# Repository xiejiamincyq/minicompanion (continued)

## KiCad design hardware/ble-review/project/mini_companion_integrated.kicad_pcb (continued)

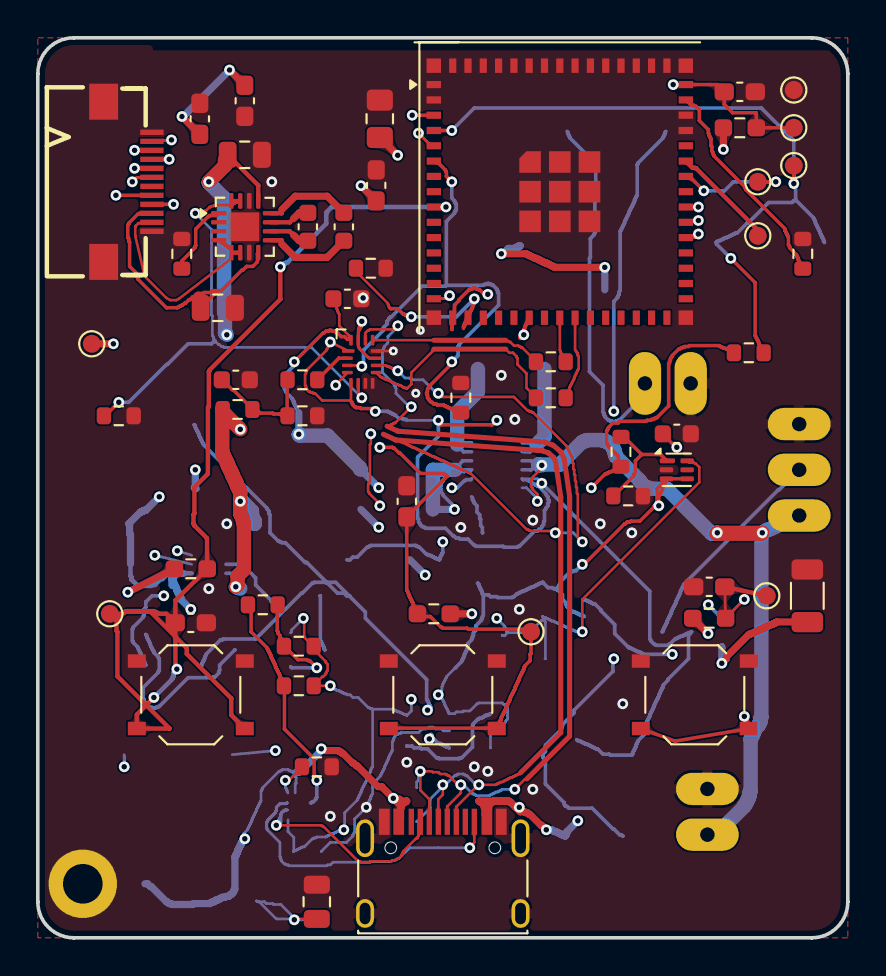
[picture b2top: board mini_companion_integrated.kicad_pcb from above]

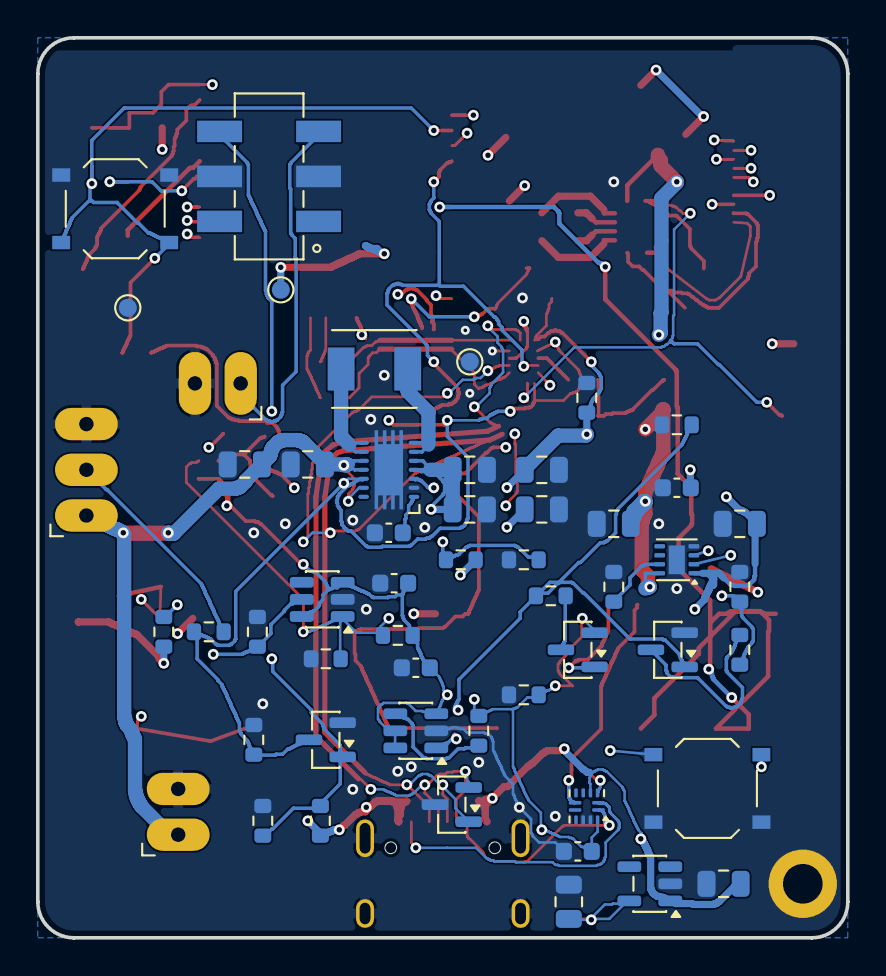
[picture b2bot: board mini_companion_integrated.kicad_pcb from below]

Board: 4 copper layers, 45.0 x 50.0 mm, 110 parts (53 on the bottom side), 58 nets.

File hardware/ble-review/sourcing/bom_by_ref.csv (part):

ref,category,assembly_domain,value,mpn,manufacturer,lcsc,footprint,qty_per_device,quantity_two,unit,source,stock_status,smt_catalog_status,source_url,note
C101,electronics,main,22µ,CL21A226MAQNNNE,Samsung,C45783,Capacitor_SMD:C_0805_2012Metric_Pad1.18x1.45mm_HandSolder,1,2,piece,saved_netlist,未取得本轮国内库存/采购报价,待嘉立创按精确型号匹配,,
C102,electronics,main,100n,CC0603KRX7R9BB104,YAGEO,C14663,Capacitor_SMD:C_0603_1608Metric_Pad1.08x0.95mm_HandSolder,1,2,piece,saved_netlist,未取得本轮国内库存/采购报价,待嘉立创按精确型号匹配,,
C103,electronics,main,1µ,CL10A105KB8NNNC,Samsung,C15849,Capacitor_SMD:C_0603_1608Metric_Pad1.08x0.95mm_HandSolder,1,2,piece,saved_netlist,未取得本轮国内库存/采购报价,待嘉立创按精确型号匹配,,
C301,electronics,main,1µ,CL10A105KB8NNNC,Samsung,C15849,Capacitor_SMD:C_0603_1608Metric_Pad1.08x0.95mm_HandSolder,1,2,piece,saved_netlist,未取得本轮国内库存/采购报价,待嘉立创按精确型号匹配,,
C302,electronics,main,1µ,CL10A105KB8NNNC,Samsung,C15849,Capacitor_SMD:C_0603_1608Metric_Pad1.08x0.95mm_HandSolder,1,2,piece,saved_netlist,未取得本轮国内库存/采购报价,待嘉立创按精确型号匹配,,
C501,electronics,main,100n,CC0603KRX7R9BB104,YAGEO,C14663,Capacitor_SMD:C_0603_1608Metric_Pad1.08x0.95mm_HandSolder,1,2,piece,saved_netlist,未取得本轮国内库存/采购报价,待嘉立创按精确型号匹配,,
C502,electronics,main,100n,CC0603KRX7R9BB104,YAGEO,C14663,Capacitor_SMD:C_0603_1608Metric_Pad1.08x0.95mm_HandSolder,1,2,piece,saved_netlist,未取得本轮国内库存/采购报价,待嘉立创按精确型号匹配,,
C504,electronics,main,100n,CC0603KRX7R9BB104,YAGEO,C14663,Capacitor_SMD:C_0603_1608Metric_Pad1.08x0.95mm_HandSolder,1,2,piece,saved_netlist,未取得本轮国内库存/采购报价,待嘉立创按精确型号匹配,,
C604,electronics,main,22uF 25V X5R 20%,CL21A226MAQNNNE,Samsung,C45783,Capacitor_SMD:C_0805_2012Metric,1,2,piece,saved_netlist,未取得本轮国内库存/采购报价,待嘉立创按精确型号匹配,,Candidate; see source contract
C606,electronics,main,22uF 25V X5R 20%,CL21A226MAQNNNE,Samsung,C45783,Capacitor_SMD:C_0805_2012Metric,1,2,piece,saved_netlist,未取得本轮国内库存/采购报价,待嘉立创按精确型号匹配,,Candidate; see source contract
C607,electronics,main,22uF 25V X5R 20%,CL21A226MAQNNNE,Samsung,C45783,Capacitor_SMD:C_0805_2012Metric,1,2,piece,saved_netlist,未取得本轮国内库存/采购报价,待嘉立创按精确型号匹配,,Candidate; see source contract
C617,electronics,main,2.2uF 10V X7R 10%,CL21B225KPFNNNE,Samsung,C107366,Capacitor_SMD:C_0805_2012Metric,1,2,piece,saved_netlist,未取得本轮国内库存/采购报价,待嘉立创按精确型号匹配,,Candidate; see source contract
C618,electronics,main,470nF 25V X7R 10%,CL10B474KA8NNNC,Samsung,C1623,Capacitor_SMD:C_0603_1608Metric,1,2,piece,saved_netlist,未取得本轮国内库存/采购报价,待嘉立创按精确型号匹配,,Candidate; see source contract
C619,electronics,main,470nF 25V X7R 10%,CL10B474KA8NNNC,Samsung,C1623,Capacitor_SMD:C_0603_1608Metric,1,2,piece,saved_netlist,未取得本轮国内库存/采购报价,待嘉立创按精确型号匹配,,Candidate; see source contract
C620,electronics,main,2.2uF 10V X7R 10%,CL21B225KPFNNNE,Samsung,C107366,Capacitor_SMD:C_0805_2012Metric,1,2,piece,saved_netlist,未取得本轮国内库存/采购报价,待嘉立创按精确型号匹配,,Candidate; see source contract
C637,electronics,main,22uF 25V X5R 20%,CL21A226MAQNNNE,Samsung,C45783,Capacitor_SMD:C_0805_2012Metric,1,2,piece,saved_netlist,未取得本轮国内库存/采购报价,待嘉立创按精确型号匹配,,Candidate; see source contract
C638,electronics,main,22uF 25V X5R 20%,CL21A226MAQNNNE,Samsung,C45783,Capacitor_SMD:C_0805_2012Metric,1,2,piece,saved_netlist,未取得本轮国内库存/采购报价,待嘉立创按精确型号匹配,,Candidate; see source contract
C639,electronics,main,100nF 50V X7R 10%,CC0603KRX7R9BB104,YAGEO,C14663,Capacitor_SMD:C_0603_1608Metric,1,2,piece,saved_netlist,未取得本轮国内库存/采购报价,待嘉立创按精确型号匹配,,Candidate; see source contract
C640,electronics,main,22uF 25V X5R 20%,CL21A226MAQNNNE,Samsung,C45783,Capacitor_SMD:C_0805_2012Metric,1,2,piece,saved_netlist,未取得本轮国内库存/采购报价,待嘉立创按精确型号匹配,,Candidate; see source contract
C1101,electronics,main,100nF 50V X7R,CC0603KRX7R9BB104,YAGEO,C14663,Capacitor_SMD:C_0603_1608Metric,1,2,piece,saved_netlist,未取得本轮国内库存/采购报价,待嘉立创按精确型号匹配,,
C1102,electronics,main,100nF 50V X7R,CC0603KRX7R9BB104,YAGEO,C14663,Capacitor_SMD:C_0603_1608Metric,1,2,piece,saved_netlist,未取得本轮国内库存/采购报价,待嘉立创按精确型号匹配,,
C7101,electronics,main,2.2uF 50V X7R 10%,CL21B225KBYNNNE,Samsung,C2762602,Capacitor_SMD:C_0805_2012Metric,1,2,piece,saved_netlist,未取得本轮国内库存/采购报价,待嘉立创按精确型号匹配,,Candidate; see source contract
C7102,electronics,main,1uF 50V X7R 10%,CL21B105KBFNNNE,Samsung,C28323,Capacitor_SMD:C_0805_2012Metric,1,2,piece,saved_netlist,未取得本轮国内库存/采购报价,待嘉立创按精确型号匹配,,Candidate; see source contract
C7103,electronics,main,2.2uF 10V X7R 10%,CL21B225KPFNNNE,Samsung,C107366,Capacitor_SMD:C_0805_2012Metric,1,2,piece,saved_netlist,未取得本轮国内库存/采购报价,待嘉立创按精确型号匹配,,Candidate; see source contract
C7104,electronics,main,2.2uF 10V X7R 10%,CL21B225KPFNNNE,Samsung,C107366,Capacitor_SMD:C_0805_2012Metric,1,2,piece,saved_netlist,未取得本轮国内库存/采购报价,待嘉立创按精确型号匹配,,Candidate; see source contract
C7105,electronics,main,100nF 50V X7R 10%,CC0603KRX7R9BB104,YAGEO,C14663,Capacitor_SMD:C_0603_1608Metric,1,2,piece,saved_netlist,未取得本轮国内库存/采购报价,待嘉立创按精确型号匹配,,Candidate; see source contract
C7106,electronics,main,100nF 50V X7R 10%,CC0603KRX7R9BB104,YAGEO,C14663,Capacitor_SMD:C_0603_1608Metric,1,2,piece,saved_netlist,未取得本轮国内库存/采购报价,待嘉立创按精确型号匹配,,Candidate; see source contract
C7107,electronics,main,100nF 50V X7R 10%,CC0603KRX7R9BB104,YAGEO,C14663,Capacitor_SMD:C_0603_1608Metric,1,2,piece,saved_netlist,未取得本轮国内库存/采购报价,待嘉立创按精确型号匹配,,Candidate; see source contract
C7108,electronics,main,2.2uF 10V X7R 10%,CL21B225KPFNNNE,Samsung,C107366,Capacitor_SMD:C_0805_2012Metric,1,2,piece,saved_netlist,未取得本轮国内库存/采购报价,待嘉立创按精确型号匹配,,Candidate; see source contract
C7301,electronics,main,100nF 50V,CC0603KRX7R9BB104,YAGEO,C14663,Capacitor_SMD:C_0603_1608Metric,1,2,piece,saved_netlist,未取得本轮国内库存/采购报价,待嘉立创按精确型号匹配,,
C7302,electronics,main,100nF 50V,CC0603KRX7R9BB104,YAGEO,C14663,Capacitor_SMD:C_0603_1608Metric,1,2,piece,saved_netlist,未取得本轮国内库存/采购报价,待嘉立创按精确型号匹配,,
D7301,electronics,main,"PESD5V0U2BT,215","PESD5V0U2BT,215",Nexperia,C85399,Package_TO_SOT_SMD:SOT-23,1,2,piece,saved_netlist,国内实时库存和人民币数量价未知,JLCPCB国际目录标Extended及SMT；国内型号匹配待询,https://jlcpcb.com/partdetail/Nexperia-PESD5V0U2BT215/C85399,
EXT_CASE_SCREWS,hardware,external,M2x6 90deg countersunk case closure screw,TBD_M2X6_90DEG_COUNTERSUNK,,,,4,8,piece,baseline_external_scope_pending_final_mechanical_review,待完整报价,板外采购或装配工序,,"Exact supplier SKU, tolerance and torque unverified; different head from switch mounting screws."
EXT_CONSUMABLES,consumables,external,Solder/flux/cleaning and general assembly consumables,TBD_ASSEMBLY_CONSUMABLE_PURCHASE,,,,0.5,1,two-device purchase batch,baseline_external_scope_pending_final_mechanical_review,待完整报价,板外采购或装配工序,,代工商提供焊料/助焊剂/清洁剂并计入加工费；此行用于确认范围，不重复采购用户零售整包耗材
EXT_DELIVERY,delivery,external,All electronics/material/PCB/printing shipment charges,TBD_ALL_REQUIRED_SHIPMENTS,,,,0.5,1,all orders,baseline_external_scope_pending_final_mechanical_review,待完整报价,板外采购或装配工序,,"One ledger placeholder covers all shipments, not a claim of one parcel. No assumed free shipping, coupons or membership discount."
EXT_H101_SCREW,hardware,external,M2x5 board fixing screw,TBD_M2X5_H101_HEAD_UNFROZEN,,,,1,2,piece,baseline_external_scope_pending_final_mechanical_review,待完整报价,板外采购或装配工序,,H101 mounting hole is already in PCB; screw head style remains unresolved. No standoffs/tray screws/independent LCD or PCB clamp screws in current assembly.
EXT_LCD,external_electronics,external,Original 2-inch display,HS20HS072RX,HS,C5329582,,1,2,piece,baseline_external_scope_pending_final_mechanical_review,本轮公开文本未返回国内数量价/可用库存,国内页面有SMT扩展库标签，但本设计为板外插屏，不可混入主板贴装坐标,https://item.szlcsc.com/6087843.html,"Retain original display; its FPC receptacle is FPC301, not duplicated here."
EXT_LCD_TAPE,insulation_fixing,external,Soft double-sided LCD mounting tape,TBD_LCD_FLEXIBLE_TAPE_0.30MM,,,,4,8,small patch,baseline_external_scope_pending_final_mechanical_review,待完整报价,板外采购或装配工序,,Nominal0.30mm thickness. Buy quantity must follow actual roll/sheet MOQ; eight patches are consumption only.
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
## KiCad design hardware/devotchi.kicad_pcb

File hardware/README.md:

> 2026-11-19 · 此页保留早期设计背景。两台 BLE 样机从 [当前硬件入口](../hardware/ble-review/README.md) 进入。

# Hardware Design

## PCB

## Device Variants

### Portable WiFi+BLE (current)
- ESP32-S3-MINI-1 with integrated PCB antenna
- HS20HS072RX 2.0" color TFT LCD (ST7789, 320x240, IPS)
- LiPo battery, USB-C charging
- 3 buttons (approve, reject, action)
- Status LED, vibration motor
- Connects to server via WiFi, or to phone via BLE

### Portable Cellular (planned)
- Same form factor as WiFi+BLE version
- Additional cellular modem (MCU TBD — may use same ESP32-S3 + SIM module, or different MCU)
- SIM/eSIM support (provider TBD)
- Works standalone anywhere with cell coverage

### Desktop (planned)
- USB-powered (no battery needed)
- Potentially larger display
- Same ESP32-S3-MINI-1, connects via USB serial or WiFi

---

## Parts

See [purchase-list.md](purchase-list.md) for the complete BOM with LCSC part numbers and sourcing info.

### MCU: ESP32-S3-MINI-1-N4R2

| Spec | Value |
|---|---|
| Part number | ESP32-S3-MINI-1-N4R2 (4MB flash, 2MB PSRAM) |
| CPU | Dual-core Xtensa LX7 @ 240 MHz |
| SRAM | 512 KB + 2MB PSRAM |
| WiFi | 802.11 b/g/n, 2.4 GHz |
| Bluetooth | BLE 5.0 |
| Antenna | Integrated PCB antenna |
| Module dimensions | 15.4 x 20.5 x 2.4 mm |
| Operating voltage | 3.0 - 3.6V |

**Datasheets:** [Module](../docs/mcu/ESP32-S3-MINI-1_datasheet.pdf) | [SoC](../docs/mcu/ESP32-S3_SoC_datasheet.pdf)

**Why N4R2:** PSRAM needed for display framebuffers — 320x240 RGB565 = 150KB per frame, double buffering needs 300KB. Without PSRAM, internal 512KB SRAM can't fit framebuffers + WiFi stack + application.

### Display: HS20HS072RX 2.0" Color TFT LCD

| Spec | Value |
|---|---|
| Manufacturer | HS (Shenzhen Hansheng) |
| Part number | HS20HS072RX |
| LCSC | C5329582 |
| Driver IC | ST7789T3 |
| Size | 2.0 inches diagonal |
| Resolution | 320 x 240 pixels (QVGA) |
| Colors | 262K (RGB666) |
| Pixel pitch | 0.151 x 0.153 mm |
| Active area | 40.80 x 30.60 mm |
| Module size | 51.80 x 36.20 mm |
| Interface | SPI (4-wire) |
| Operating voltage | IOVCC 1.65-3.3V, VCI 2.4-3.3V |
| Backlight | 4 white LEDs in parallel, 80mA max |
| Backlight forward voltage | 3.0V typical (2.8-3.2V) |
| Sleep current | ~30 uA (SLPIN command) |
| Viewing angle | ALL directions (IPS) |
| Contrast ratio | 300:1 typical |
| Connector | 12-pin FPC, 0.5mm pitch |
| Connection type | COG + FPC |

**Datasheet:** [HS20HS072RX datasheet](../docs/display/HS20HS072RX_datasheet.pdf)

**Source:** [LCSC/JLCPCB C5329582](https://www.lcsc.com/product-detail/lcd-screen_hs-hs20hs072rx_C5329582.html) — $3.70 (1+), $2.49 (100+), 1687 in stock.

**Why this part:**
- Full RGB color — expressive Tamagotchi character (red angry, green happy, etc.)
- 320x240 resolution — excellent detail for pixel art and text
- IPS viewing angle — looks good from any direction (critical for handheld)
- Runs entirely on 3.3V — no boost converter needed (unlike OLED panels needing 12V VCC)
- ST7789 has first-class ESP-IDF support via built-in `esp_lcd` driver
- $2.49 at volume with 1600+ stock — cheap and available
- 12-pin FPC is simple to wire (vs 30-pin for OLED panels)
- Backlight can be PWM-dimmed via MOSFET for power saving

**FPC pinout:**

| Pin | Symbol | Description |
|---|---|---|
| 1 | GND | Power ground |
| 2 | CS | Chip select (active low) |
| 3 | RS (DC) | Data/command select |
| 4 | SCL | SPI clock |
| 5 | SDA | SPI data (MOSI) |
| 6 | RST | Reset (active low) |
| 7 | NC | No connect |
| 8 | IOVCC | I/O logic supply (3.3V) |
| 9 | VCC | Panel power supply (3.3V) |
| 10 | A | Backlight LED anode |
| 11 | K | Backlight LED cathode |
| 12 | GND | Power ground |

### Backlight Dimming Circuit

Backlight driven from +BATT (3.7-4.2V) through 22Ω resistor + AO3400A N-ch MOSFET, PWM-controlled by ESP32.

**Why +BATT instead of 3.3V:** LEDs have Vf = 3.0V. Only 0.3V headroom from 3.3V — poor regulation. +BATT gives 0.7-1.2V headroom.

**Circuit:** `+BATT → R (22Ω) → LED anode → LED cathode → MOSFET drain → GND`, gate driven by DISP_BL GPIO.

**Current at different battery voltages:**
- 4.2V (full): ~55mA | 3.7V (nominal): ~32mA | 3.4V (low): ~18mA

**Firmware:** PWM at 1kHz+. Sleep: SLPIN (0x10) + duty=0. Wake: duty>0 + SLPOUT (0x11), wait 120ms.

### Firmware Graphics Library

**Recommended: ESP-IDF native `esp_lcd` + LovyanGFX**

- `esp_lcd` provides the built-in ST7789 panel driver for SPI initialization
- LovyanGFX provides sprite-based graphics, text rendering, and animations
- LovyanGFX supports ESP-IDF natively (not Arduino-only)
- Supports DMA transfers for background rendering
- ST7789 sleep commands (SLPIN/SLPOUT) supported for power management
- Alternative: LVGL if more complex UI widgets are needed later

### Power Chain

USB-C → TP4056 (charger) → DW01A+FS8205A (protection) → ME6211 (3.3V LDO) → ESP32-S3 + display

**Datasheets:** [TP4056](../docs/power/TP4056_datasheet.pdf) | [DW01A](../docs/power/DW01A_datasheet.pdf) | [FS8205A](../docs/power/FS8205A_datasheet.pdf) | [ME6211](../docs/power/ME6211_datasheet.pdf)

**Key design notes:**
- TP4056 charge current set by R205 (3kΩ → ~330mA charge rate)
- DW01A+FS8205A: standard LiPo protection pair, back-to-back MOSFETs in battery ground path
- ME6211 LDO: 100mV dropout — at low battery (<3.4V) output sags below 3.3V, acceptable for MVP
- USB-C CC1/CC2 pull-downs: 5.1kΩ each for proper USB-C detection

### Buttons

3 tactile switches with hardware debounce (10kΩ pull-up + 100nF cap per button). Active low, pressed = GND. Any button press wakes from deep sleep.

| Button | Function |
|---|---|
| Approve | Accept approval/permission requests |
| Reject | Reject approval/permission requests |
| Action | Context-dependent: scroll, open menu, poke pet |

### Feedback

- **Debug LED** (green 0603) — GPIO direct drive through 150Ω resistor. Dev/debug only.
- **Vibration motor** (6mm coin, 3V) — AO3400A MOSFET driver + 1N5819W flyback diode. PWM-capable. Connected via solder pads.

---

## Pin Assignment

**Strapping pins to avoid:** GPIO0 (boot mode), GPIO3 (JTAG source, floating), GPIO45 (VDD_SPI), GPIO46 (boot mode). These are sampled at reset and should not have external loads that could affect their default state during boot.

| Function | ESP32-S3 GPIO | Notes |
|---|---|---|
| **SPI Display** | | |
| DISP_SCLK | GPIO 12 | SPI clock |
| DISP_MOSI | GPIO 11 | SPI data |
| DISP_CS | GPIO 10 | Chip select |
| DISP_DC | GPIO 9 | Data/command select |
| DISP_RST | GPIO 8 | Reset |
| DISP_BL | GPIO 13 | PWM via MOSFET to backlight cathode |
| **Buttons** | | |
| BTN_APPROVE | GPIO 4 | Pull-up, active low |
| BTN_REJECT | GPIO 5 | Pull-up, active low |
| BTN_ACTION | GPIO 6 | Pull-up, active low |
| **Feedback** | | |
| LED_PWM | GPIO 38 | PWM for brightness control |
| MOTOR_EN | GPIO 37 | Via N-channel MOSFET |
| **Power status** | | |
| PWR_CHRG | GPIO 18 | Low = charging |
| PWR_STDBY | GPIO 17 | Low = charge complete |
| BAT_ADC | GPIO 1 | Via voltage divider for battery level |
| **Future (unused, reserved)** | | |
| I2S BCLK | GPIO 15 | For microphone (voice commands) |
| I2S WS | GPIO 16 | For microphone |
| I2S DIN | GPIO 2 | For microphone (GPIO 17 used by PWR_STDBY) |

---

## Power Budget (estimated)

| State | ESP32-S3 | Display | Total | Battery life (500mAh) |
|---|---|---|---|---|
| **Active** (WiFi on, display on, backlight 100%) | ~80 mA | ~60 mA | ~140 mA | ~3.6 hours |
| **Idle** (WiFi connected, backlight 25%) | ~20 mA | ~15 mA | ~35 mA | ~14 hours |
| **Light sleep** (WiFi off, backlight off, LCD sleep) | ~2 mA | ~0.03 mA | ~2 mA | ~250 hours |
| **Deep sleep** (everything off) | ~8 uA | ~30 uA | ~38 uA | ~1.5 years |

Real-world usage will be a mix — display on for a few seconds when events arrive, then back to sleep. Expected practical battery life: **2-5 days** with typical AI coding session activity.

---

## Power Management Strategy

1. **Normal operation**: WiFi connected, display off. ESP32 in light sleep between events.
2. **Event arrives** (via WiFi): Wake up, turn on display, show status/approval, vibrate if needed.
3. **Approval request**: Display stays on with countdown timer until user responds or timeout.
4. **No activity for N minutes**: Enter deep sleep. Wake on any button press.
5. **Deep sleep**: Everything off. Battery lasts weeks/months.
6. **Display auto-off**: Display turns off after 30 seconds of no new events (configurable).

---

## PCB Design Notes

- **Single PCB** — power management and logic on one board
- Power section (TP4056, ME6211, USB-C, battery connector) on one side, logic section (ESP32, display connector, buttons) on the other
- Ground plane between sections
- ESP32-S3-MINI-1 antenna keepout zone respected (no copper/ground under antenna area)
- Display connects via 12-pin 0.5mm FPC cable (AFC01-S12FCA-00 connector)
- USB-C connector: 16-pin mid-mount type with D+/D- connected to ESP32-S3 USB OTG pins for firmware updates and serial communication
- Battery connector: JST-PH 2-pin SMD (standard for small LiPo, LCSC C7433648)
- Test points: 3.3V, +BATT, GND, UART TX/RX

---

## Enclosure

- 3D printed (material TBD: PLA, ABS, or PETG)
- Size determined after PCB layout and LiPo selection
- Rough estimate: ~50 x 40 x 20mm (similar to original Tamagotchi)
- Cutouts for: display window, 4 buttons, USB-C port, LED light pipe
- Optional clip or lanyard hole for portability

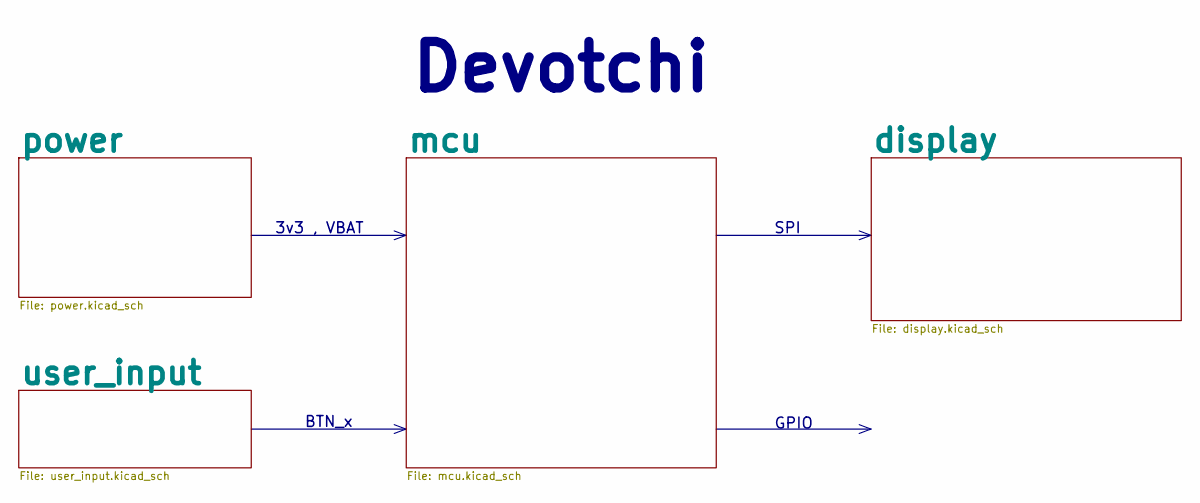
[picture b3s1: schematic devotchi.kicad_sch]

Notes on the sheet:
Devotchi
3v3 , VBAT
GPIO
SPI
BTN_x

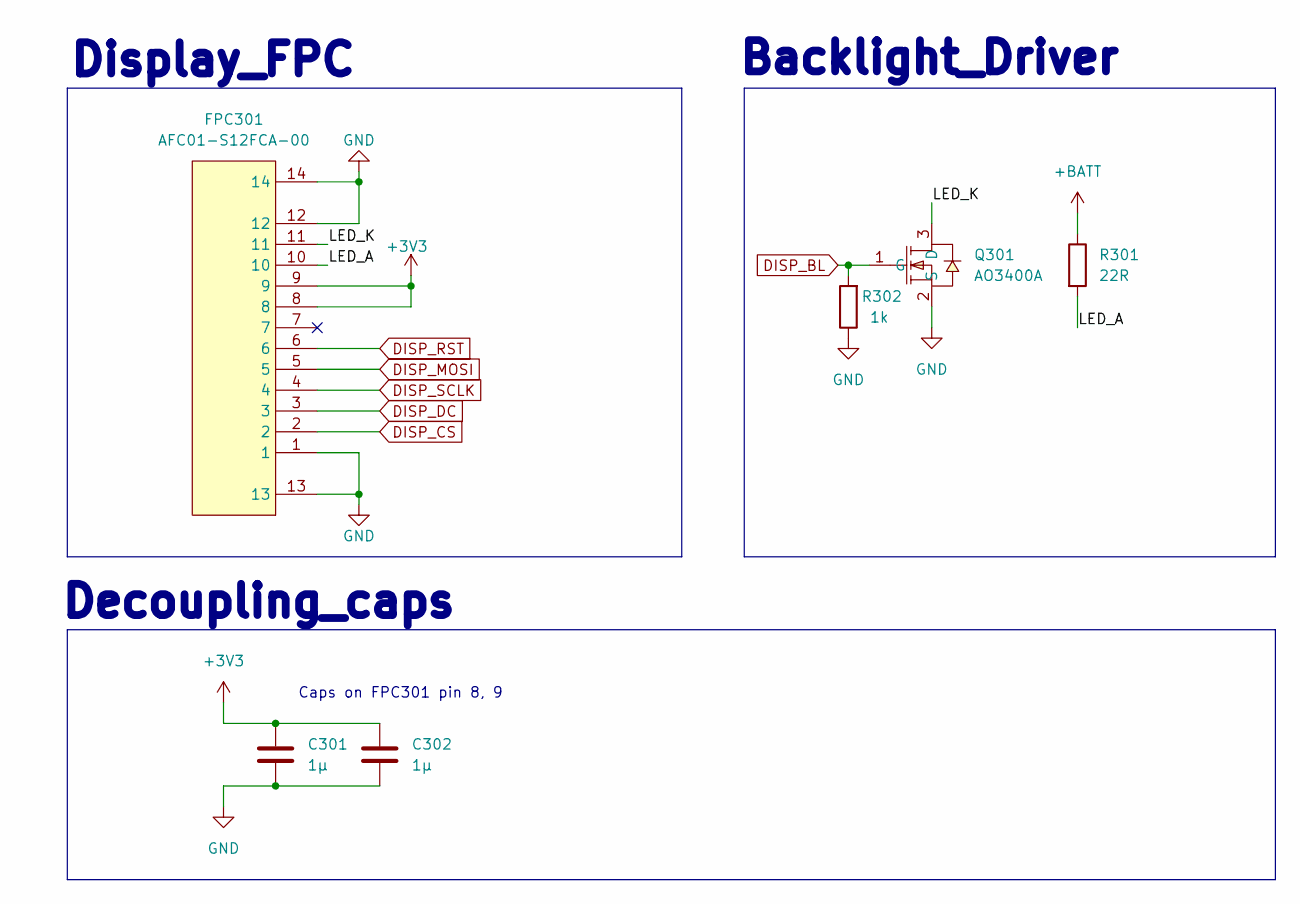
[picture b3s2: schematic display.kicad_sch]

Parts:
C301, C302: 1µ; C_0603_1608Metric_Pad1.08x0.95mm_HandSolder; LCSC Part C15849
FPC301: AFC01-S12FCA-00; FPC-SMD_AFC01-S12FCA-00; LCSC Part C262661
Q301: AO3400A; SOT-23-3_L2.9-W1.3-P1.90-LS2.4-BR; LCSC Part C20917
R301: 22R; R_0603_1608Metric_Pad0.98x0.95mm_HandSolder; LCSC Part C23345
R302: 1k; R_0603_1608Metric_Pad0.98x0.95mm_HandSolder; LCSC Part C21190

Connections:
+3V3: C301.1, C302.1, FPC301.8, FPC301.9; also elsewhere on the board
+BATT: R301.1; also elsewhere on the board
/display/LED_A: FPC301.10, R301.2
/display/LED_K: FPC301.11, Q301.3 (D)
DISP_BL: Q301.1 (G), R302.2; also elsewhere on the board
DISP_CS: FPC301.2; also elsewhere on the board
DISP_DC: FPC301.3; also elsewhere on the board
DISP_MOSI: FPC301.5; also elsewhere on the board
DISP_RST: FPC301.6; also elsewhere on the board
DISP_SCLK: FPC301.4; also elsewhere on the board
GND: C301.2, C302.2, FPC301.1, FPC301.12, FPC301.13, FPC301.14, Q301.2 (S), R302.1; also elsewhere on the board

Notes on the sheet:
Decoupling_caps
Caps on FPC301 pin 8, 9
Display_FPC
Backlight_Driver

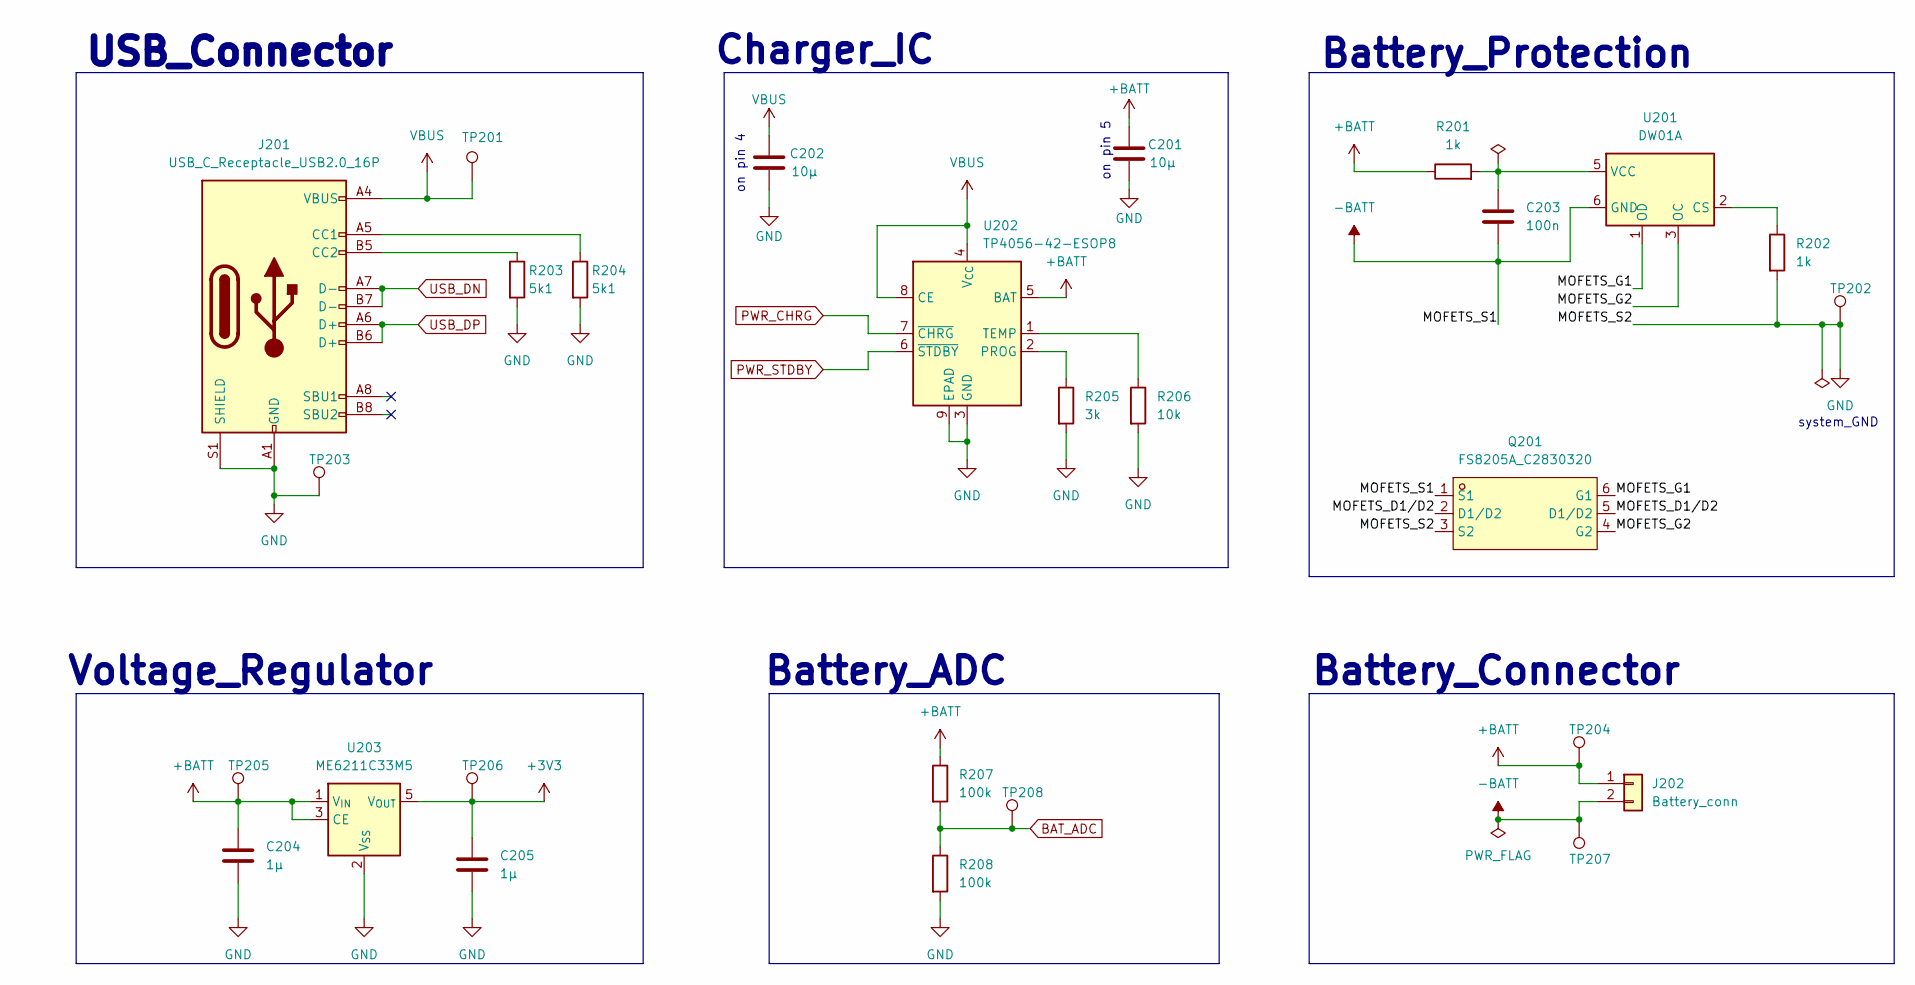
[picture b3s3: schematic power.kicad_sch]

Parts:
C201, C202: 10µ; C_0805_2012Metric_Pad1.18x1.45mm_HandSolder; LCSC Part C15850
C203: 100n; C_0603_1608Metric_Pad1.08x0.95mm_HandSolder; LCSC Part C14663
C204, C205: 1µ; C_0603_1608Metric_Pad1.08x0.95mm_HandSolder; LCSC Part C15849
J201: USB_C_Receptacle_USB2.0_16P; USB_C_Receptacle_HRO_TYPE-C-31-M-12; LCSC Part C165948
J202: Battery_conn; JST_PH_S2B-PH-SM4-TB_1x02-1MP_P2.00mm_Horizontal; LCSC Part C7433648
Q201: FS8205A_C2830320; SOT-23-6_L2.9-W1.6-P0.95-LS2.8-BR; LCSC Part C2830320
R201, R202: 1k; R_0603_1608Metric_Pad0.98x0.95mm_HandSolder; LCSC Part C21190
R203, R204: 5k1; R_0603_1608Metric_Pad0.98x0.95mm_HandSolder; LCSC Part C23186
R205: 3k; R_0603_1608Metric_Pad0.98x0.95mm_HandSolder; LCSC Part C4211
R206: 10k; R_0603_1608Metric_Pad0.98x0.95mm_HandSolder; LCSC Part C25804
R207, R208: 100k; R_0603_1608Metric_Pad0.98x0.95mm_HandSolder; LCSC Part C25803
TP201, TP202, TP203, TP204, TP205, TP206, TP207, TP208: TestPoint; TestPoint_Pad_D1.0mm
U201: DW01A; SOT-23-6; LCSC Part C351410
U202: TP4056-42-ESOP8; SOIC-8-1EP_3.9x4.9mm_P1.27mm_EP2.41x3.3mm_ThermalVias; LCSC Part C725790
U203: ME6211C33M5; SOT-23-5; LCSC Part C82942

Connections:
+3V3: C205.1, TP206.1, U203.5 (V_{OUT}); also elsewhere on the board
+BATT: C201.1, C204.1, J202.1, R201.1, R207.1, TP204.1, TP205.1, U202.5 (BAT), U203.1 (V_{IN}), U203.3 (CE); also elsewhere on the board
-BATT: C203.2, J202.2, Q201.1 (S1), TP207.1, U201.6 (GND)
/power/MOFETS_D1/D2: Q201.2 (D1/D2), Q201.5 (D1/D2)
/power/MOFETS_G1: Q201.6 (G1), U201.1 (OD)
/power/MOFETS_G2: Q201.4 (G2), U201.3 (OC)
BAT_ADC: R207.2, R208.1, TP208.1; also elsewhere on the board
GND: C201.2, C202.2, C204.2, C205.2, J201.A1 (GND), J201.A12 (GND), J201.B1 (GND), J201.B12 (GND), J201.S1 (SHIELD), Q201.3 (S2), R202.2, R203.2, R204.2, R205.2, R206.2, R208.2, TP202.1, TP203.1, U202.3 (GND), U202.9 (EPAD), U203.2 (V_{SS}); also elsewhere on the board
unnamed: J201.A5 (CC1), R204.1
unnamed: J201.B5 (CC2), R203.1
unnamed: R202.1, U201.2 (CS)
unnamed: C203.1, R201.2, U201.5 (VCC)
unnamed: R205.1, U202.2 (PROG)
unnamed: R206.1, U202.1 (TEMP)
PWR_CHRG: U202.7 (~CHRG); also elsewhere on the board
PWR_STDBY: U202.6 (~STDBY); also elsewhere on the board
USB_DN: J201.A7 (D-), J201.B7 (D-); also elsewhere on the board
USB_DP: J201.A6 (D+), J201.B6 (D+); also elsewhere on the board
VBUS: C202.1, J201.A4 (VBUS), J201.A9 (VBUS), J201.B4 (VBUS), J201.B9 (VBUS), TP201.1, U202.4 (V_{CC}), U202.8 (CE)

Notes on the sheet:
on pin 4
system_GND
Battery_Connector
Battery_Protection
USB_Connector
on pin 5
Battery_ADC
Voltage_Regulator
Charger_IC

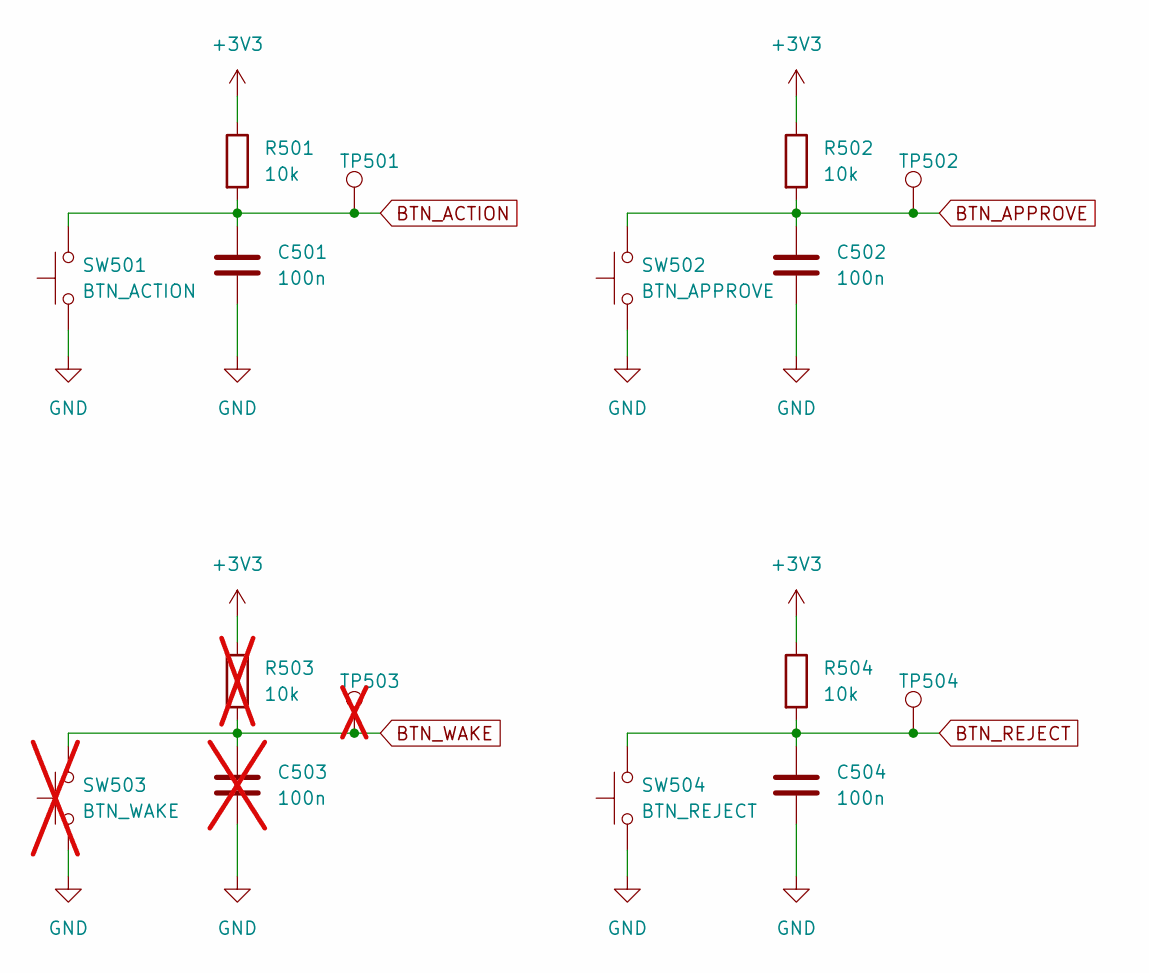
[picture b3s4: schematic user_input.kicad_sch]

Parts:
C501, C502, C504: 100n; C_0603_1608Metric_Pad1.08x0.95mm_HandSolder; LCSC Part C14663
C503: 100n; C_0603_1608Metric_Pad1.08x0.95mm_HandSolder; LCSC Part C14663; not fitted
R501, R502, R504: 10k; R_0603_1608Metric_Pad0.98x0.95mm_HandSolder; LCSC Part C25804
R503: 10k; R_0603_1608Metric_Pad0.98x0.95mm_HandSolder; LCSC Part C25804; not fitted
SW501: BTN_ACTION; SW_Push_1P1T_XKB_TS-1187A; LCSC Part C318884
SW502: BTN_APPROVE; SW_Push_1P1T_XKB_TS-1187A; LCSC Part C318884
SW503: BTN_WAKE; SW_Push_1P1T_XKB_TS-1187A; LCSC Part C318884; not fitted
SW504: BTN_REJECT; SW_Push_1P1T_XKB_TS-1187A; LCSC Part C318884
TP501, TP502, TP504: TestPoint; TestPoint_Pad_D1.0mm
TP503: TestPoint; TestPoint_Pad_D1.0mm; not fitted

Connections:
+3V3: R501.1, R502.1, R503.1, R504.1; also elsewhere on the board
BTN_ACTION: C501.1, R501.2, SW501.2, TP501.1; also elsewhere on the board
BTN_APPROVE: C502.1, R502.2, SW502.2, TP502.1; also elsewhere on the board
BTN_REJECT: C504.1, R504.2, SW504.2, TP504.1; also elsewhere on the board
GND: C501.2, C502.2, C503.2, C504.2, SW501.1, SW502.1, SW503.1, SW504.1; also elsewhere on the board
unnamed: C503.1, R503.2, SW503.2, TP503.1

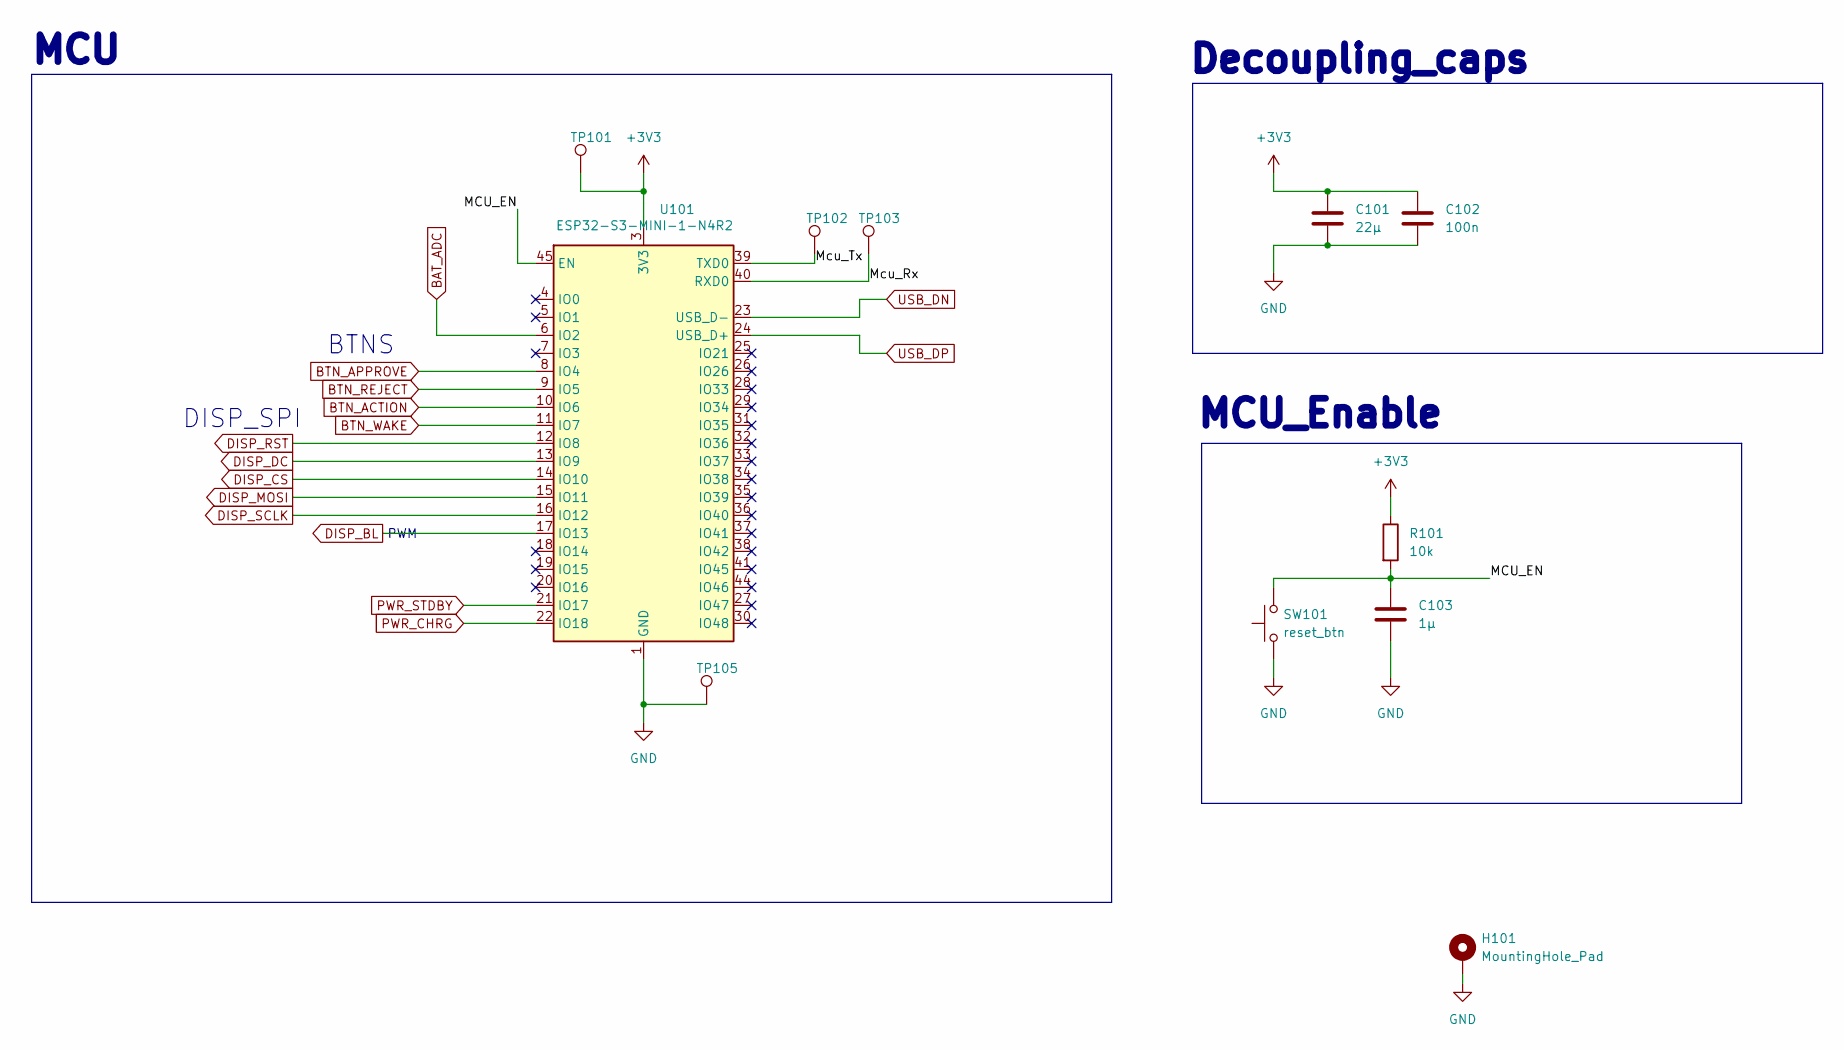
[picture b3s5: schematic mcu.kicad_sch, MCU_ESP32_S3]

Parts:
C101: 22µ; C_0805_2012Metric_Pad1.18x1.45mm_HandSolder; LCSC Part C45783
C102: 100n; C_0603_1608Metric_Pad1.08x0.95mm_HandSolder; LCSC Part C14663
C103: 1µ; C_0603_1608Metric_Pad1.08x0.95mm_HandSolder; LCSC Part C15849
H101: MountingHole_Pad; MountingHole_2.2mm_M2_DIN965_Pad
R101: 10k; R_0603_1608Metric_Pad0.98x0.95mm_HandSolder; LCSC Part C25804
SW101: reset_btn; SW_Push_1P1T_XKB_TS-1187A; LCSC Part C318884
TP101, TP105: TestPoint; TestPoint_Pad_D1.0mm
TP102: Tx; TestPoint_Pad_D1.0mm
TP103: Rx; TestPoint_Pad_D1.0mm
U101: ESP32-S3-MINI-1-N4R2; ESP32-S2-MINI-1; LCSC Part C3013941

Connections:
+3V3: C101.1, C102.1, R101.1, TP101.1, U101.3 (3V3); also elsewhere on the board
/mcu/MCU_EN: C103.1, R101.2, SW101.2, U101.45 (EN)
/mcu/Mcu_Rx: TP103.1, U101.40 (RXD0)
/mcu/Mcu_Tx: TP102.1, U101.39 (TXD0)
BAT_ADC: U101.6 (IO2); also elsewhere on the board
BTN_ACTION: U101.10 (IO6); also elsewhere on the board
BTN_APPROVE: U101.8 (IO4); also elsewhere on the board
BTN_REJECT: U101.9 (IO5); also elsewhere on the board
BTN_WAKE: U101.11 (IO7)
DISP_BL: U101.17 (IO13); also elsewhere on the board
DISP_CS: U101.14 (IO10); also elsewhere on the board
DISP_DC: U101.13 (IO9); also elsewhere on the board
DISP_MOSI: U101.15 (IO11); also elsewhere on the board
DISP_RST: U101.12 (IO8); also elsewhere on the board
DISP_SCLK: U101.16 (IO12); also elsewhere on the board
GND: C101.2, C102.2, C103.2, H101.1, SW101.1, TP105.1, U101.1 (GND), U101.2 (GND), U101.42 (GND), U101.43 (GND), U101.46 (GND), U101.47 (GND), U101.48 (GND), U101.49 (GND), U101.50 (GND), U101.51 (GND), U101.52 (GND), U101.53 (GND), U101.54 (GND), U101.55 (GND), U101.56 (GND), U101.57 (GND), U101.58 (GND), U101.59 (GND), U101.60 (GND), U101.61 (GND), U101.62 (GND), U101.63 (GND), U101.64 (GND), U101.65 (GND); also elsewhere on the board
PWR_CHRG: U101.22 (IO18); also elsewhere on the board
PWR_STDBY: U101.21 (IO17); also elsewhere on the board
USB_DN: U101.23 (USB_D-); also elsewhere on the board
USB_DP: U101.24 (USB_D+); also elsewhere on the board

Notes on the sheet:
BTNS
DISP_SPI
Decoupling_caps
MCU_Enable
PWM
MCU

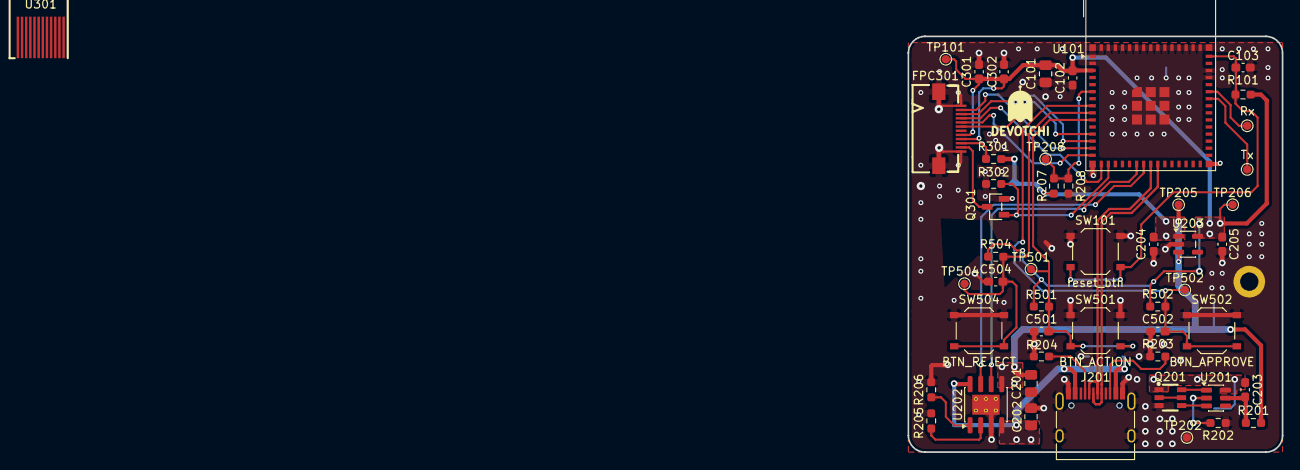
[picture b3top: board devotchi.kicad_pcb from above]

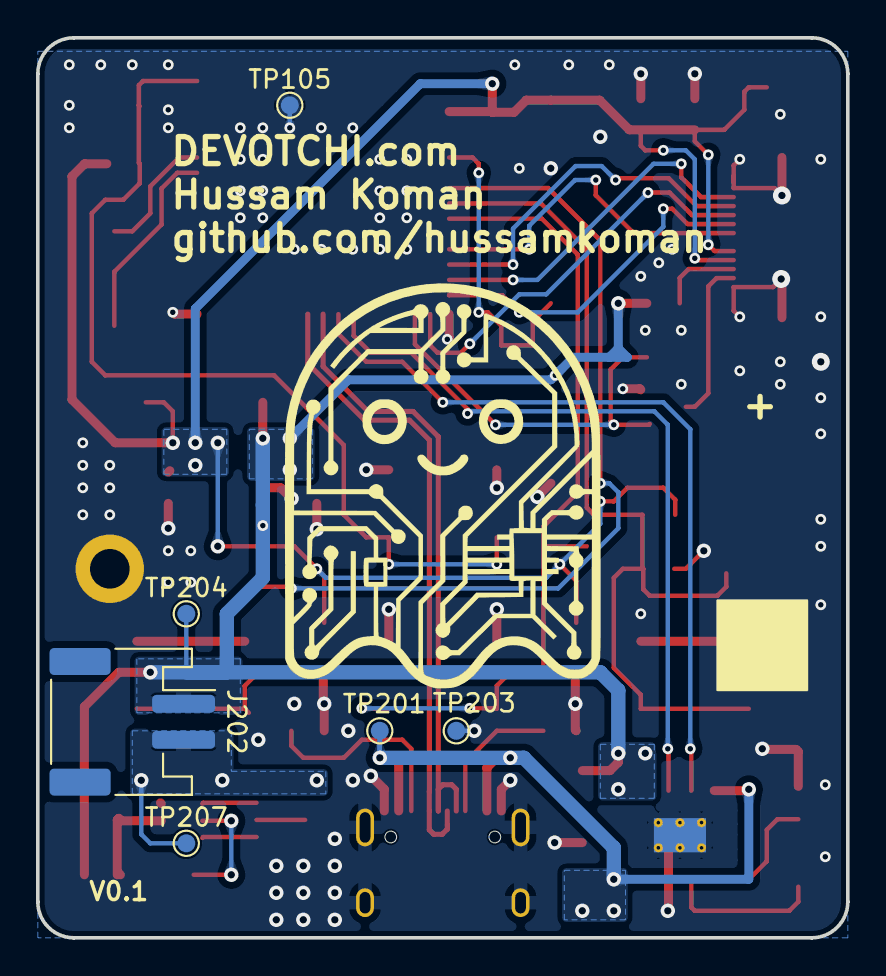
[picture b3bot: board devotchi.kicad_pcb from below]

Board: 4 copper layers, 45.0 x 50.0 mm, 57 parts (6 on the bottom side), 33 nets.

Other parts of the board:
U301: HS20HS072RX; OLED-SMD_HS20HS072RX

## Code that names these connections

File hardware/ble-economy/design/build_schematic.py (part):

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add('U2','TPS61023DRLR','TPS61023 / true shutdown','Package_TO_SOT_SMD:SOT-563','TPS61023DRLR','C919459',(265,185),{'1':'BOOST_FB','2':'RUN_EN','3':'PACK_POS','4':'GND','5':'BOOST_SW','6':'RUN_5V'},maker='Texas Instruments')
cap('C4','22uF 25V','CL21A226MAQNNNE','C45783',(350,185),'RUN_5V')
cap('C5','22uF 25V','CL21A226MAQNNNE','C45783',(420,185),'RUN_5V')
add('J4','Conn_01x02','RUN USB-C power lead',PH2,'B2B-PH-SM4-TB(LF)(SN)','C160352',(520,185),{'1':'RUN_5V','2':'GND'},maker='JST')
resistor('R6','220k 1%','0603WAF2203T5E','C22961',(350,230),'RUN_5V','BOOST_FB')
resistor('R7','30k 1%','0603WAF3002T5E','C22984',(420,230),'BOOST_FB','GND')
resistor('R8','10k bleed','0603WAF1002T5E','C25804',(520,230),'RUN_5V','GND')
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add('J5','Conn_01x05','CORE keys + 5V sense','Connector_JST:JST_PH_B5B-PH-SM4-TB_1x05-1MP_P2.00mm_Vertical','B5B-PH-SM4-TB(LF)(SN)','C265085',(520,310),{'1':'GND','2':'KEY_A','3':'KEY_B','4':'KEY_C','5':'CORE_5V_SENSE'},maker='JST')
for i,key in enumerate(['KEY_A','KEY_B','KEY_C'],1):
    add('SW'+str(i),'SW_Push',key+' / dry contact','Button_Switch_SMD:SW_Push_1P1T_XKB_TS-1187A','TS-1187A-B-A-B','C318884',(40+70*(i-1),365),{'1':key,'2':'GND'},maker='XKB')
text('Core harness: KEY_A=GPIO2/P1.1; KEY_B=GPIO4/P1.2; KEY_C=GPIO7/P1.9; sense=P1.14(5V).\nNo carrier-side key pull-ups. Do not connect core BAT/VBAT. Permanent labelled harness; sense-open is an explicit fault boundary.',250,357)
for n,(net,pos) in enumerate([('GND',(270,385)),('DC_PROTECTED',(420,385)),('UVLO_VDD',(350,385))],1):
    add('#FLG0'+str(n),'PWR_FLAG','PWR_FLAG','','','',pos,{'1':net},domain='annotation')
library=[A('kicad_symbol_lib'),[A('version'),A('20231120')],[A('generator'),'eeschema']]+list(syms.values())
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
